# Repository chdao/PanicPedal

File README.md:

# PanicPedal

A wireless pedal system using ESP-NOW for low-latency communication between pedal transmitters and a USB HID keyboard receiver. Perfectly adequate for arcade gaming!

**Original Design**: This project is based on the [Perfectly Adequate Arcade Pedal (Wireless)](https://www.printables.com/model/1220746-perfectly-adequate-arcade-pedal-wireless) design on Printables. All initial ideas and the pedal model come from that design.

**PCB Project**: The custom PCB design is called **PanicPedal Pro** and includes an ESP32-S3-WROOM with automatic pedal detection. See `kicad-pcb/` for the KiCad project files and `esp32/panicpedal-pro/` for the firmware.

**⚠️ IMPORTANT CORRECTION**: The original schematic shows TP4056 OUT+ connected to the 3V3 pin. This is **INCORRECT** and can damage the ESP32. The TP4056 OUT+ must connect to **VCC** instead. See the [Wiring Diagram](#wiring-diagram) section below for the correct connections.

## Overview

This project consists of:
- **Transmitters**: ESP32-based pedal devices that send key press/release events via ESP-NOW
  - **FireBeetle 2**: `esp32/firebeetle2/firebeetle2.ino` - Configurable single or dual pedal mode
  - **PanicPedal Pro**: `esp32/panicpedal-pro/panicpedal-pro.ino` - Custom PCB with automatic pedal detection (1 or 2 pedals)
- **Receiver**: ESP32-S2/S3 device that receives ESP-NOW messages and types keys via USB HID Keyboard (`esp32/receiver/receiver.ino`)

**Note**: `espnow-pedal.cpp` is included as a reference file showing the original implementation. The actual project files are in the `esp32/` directory.

## Features

- **Low latency**: ESP-NOW provides fast, direct communication without WiFi connection
- **Multiple pedal modes**: Supports single pedal (LEFT or RIGHT) or dual pedal configurations
- **Automatic pedal detection** (PanicPedal Pro): Automatically detects whether 1 or 2 pedals are connected using NC (normally-closed) contacts - no manual configuration needed
- **Press and hold**: Keys stay pressed until pedal is released
- **Independent operation**: Both pedals can be pressed simultaneously
- **Battery efficient**: Includes inactivity timeout and deep sleep support
- **Automatic discovery**: No manual MAC address configuration needed - transmitters automatically discover receivers
- **Automatic reconnection**: Transmitters automatically reconnect to receivers after reboot
- **Slot management**: Receiver tracks available slots and only accepts transmitters when slots are available
- **Grace period**: 30-second discovery period after receiver boot for initial pairing and verification

## Hardware Requirements

### Recommended Boards

**Transmitters:**
- [FireBeetle 2 ESP32-E](https://www.dfrobot.com/product-2195.html) - Optimized for low power consumption, ideal for battery-powered pedal transmitters
- **PanicPedal Pro** - Custom PCB project with ESP32-S3-WROOM featuring automatic pedal detection (see `esp32/panicpedal-pro/README.md` for details)

**Receiver:**
- [ESP32-S3-DevKitC-1-N16R8](https://www.amazon.com/dp/B0CC8NYXRG) - ESP32-S3 board with native USB support for HID Keyboard functionality

### Transmitter
- ESP32 (tested with FireBeetle 2 ESP32-E and ESP32-S3-WROOM for PanicPedal Pro)
- Pedal switches (normally-open, connected to GPIO with pull-up)
- Optional: LED for status indication
- **PanicPedal Pro**: Uses NC (normally-closed) contacts for automatic detection of connected pedals

### Receiver
- ESP32-S2 or ESP32-S3 (for USB HID Keyboard support)
- USB connection to computer

## Pin Configuration

### Transmitter
- **Single Pedal Mode**: Connect pedal switch to GPIO 13
- **Dual Pedal Mode**: 
  - LEFT pedal: GPIO 13
  - RIGHT pedal: GPIO 14
- **LED**: GPIO 2 (optional)

**Pinout Reference**: See [FireBeetle 2 ESP32-E Pinout](docs/FireBeetle2_ESP32-E_Pinout.md) for complete pin details.

### Receiver
- Uses USB for communication (no GPIO pins needed for functionality)

## Wiring Diagram

### Transmitter Power Wiring (FireBeetle 2 ESP32-E)

**⚠️ IMPORTANT**: The TP4056 charging board OUT+ must connect to **VCC**, NOT 3V3!

```
TP4056 Charging Board          FireBeetle 2 ESP32-E
─────────────────────          ─────────────────────
OUT+ (red wire)    ──────────> VCC (or PH2.0 battery connector)
OUT- (black wire)  ──────────> GND
B+                 ──────────> 18650 Battery +
B-                 ──────────> 18650 Battery -
IN+                ──────────> Power Switch
IN-                ──────────> GND
```

**Why VCC and not 3V3?**
- **VCC** is the input voltage pin that accepts battery voltage (3.7-4.2V) or USB voltage (~4.7V)
- **3V3** is a regulated 3.3V OUTPUT pin - connecting 4-5V to it can damage the ESP32
- The FireBeetle's onboard regulator converts VCC to 3.3V internally

### Transmitter Signal Wiring

```
Left Pedal Switch (NO)  ───> GPIO 13
Left Pedal Switch (COM) ───> GND

Right Pedal Switch (NO)  ───> GPIO 14 (dual mode only)
Right Pedal Switch (COM) ───> GND

LED (anode)            ───> GPIO 2 (optional)
LED (cathode)          ───> GND
```

**Note**: The original schematic may show a "Mode Select Switch" on GPIO 26 for selecting between Bluetooth and ESP-NOW modes. This code uses ESP-NOW only, so that switch is not needed. Pedal mode (single/dual) is configured via the `PEDAL_MODE` define in the code.

**Note**: Switches should be normally-open (NO) type. The ESP32's internal pull-up resistors keep the pins HIGH when switches are open, and LOW when pressed.

## Setup and Usage

For detailed setup instructions, usage guide, configuration options, debug monitor setup, and troubleshooting, see [INSTRUCTIONS.md](INSTRUCTIONS.md).

## License

This project is provided as-is for educational and personal use.

## Contributing

Feel free to submit issues or pull requests for improvements!

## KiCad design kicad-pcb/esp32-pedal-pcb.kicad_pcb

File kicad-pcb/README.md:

# ESP32 Pedal PCB Design

KiCad project for a custom ESP32-based pedal PCB.

## Images

*Complete schematic diagram*

*PCB layout and routing*

*3D visualization of the PCB*

*Reference: FireBeetle 2 ESP32-E board (for comparison)*

## Specifications

- **Board Size**: 215.9mm x 25.4mm (8.5" x 1")
- **MCU**: ESP32-S3-WROOM-1 (native USB support)
- **Power**: USB-C charging + LiPo battery
- **Features**:
  - USB-C port (charging + data/programming)
  - Battery charging with TP4056
  - Battery voltage monitoring (ADC)
  - Status LED (green)
  - RGB LED (charger status, user-controllable)
  - Auto-reset circuit
  - Battery protection

## Circuit Sections

### 1. Power Management
- **USB-C Input**: VBUS with 5.1kΩ CC pull-downs
- **Battery Charger**: TP4056 (500mA charging current)
- **Battery Protection**: DW01A + FS8205A MOSFETs
- **3.3V Regulator**: AMS1117-3.3 or AP2112K-3.3
- **Battery Monitor**: Voltage divider (2x 100kΩ) to GPIO34

### 2. ESP32-S3-WROOM-1
- Native USB support (no USB-UART bridge needed)
- USB D+/D- connected directly to ESP32-S3
- Auto-reset circuit (DTR/RTS control)
- Boot button (GPIO0)
- Reset button (EN)

### 3. LEDs
- **Green Status LED**: GPIO2 → 330Ω → LED → GND
- **RGB LED**: 
  - Red: GPIO16 → 330Ω → R pin
  - Green: GPIO17 → 330Ω → G pin
  - Blue: GPIO18 → 330Ω → B pin
  - Common cathode → GND

### 4. Battery Monitoring
- Battery voltage divider: VBAT → 100kΩ → GPIO34 → 100kΩ → GND
- Charger status: TP4056 STAT pin → GPIO35

## GPIO Assignments

```
GPIO0:  Boot button (pulled high, button to GND)
GPIO2:  Green status LED
GPIO16: RGB LED - Red
GPIO17: RGB LED - Green  
GPIO18: RGB LED - Blue
GPIO21: Pedal switch
GPIO34: Battery voltage (ADC, input only)
GPIO35: Charger status (ADC, input only)
EN:     Reset button (pulled high, button to GND)
```

## Components List (BOM)

### ICs
- U1: ESP32-S3-WROOM-1 (or WROOM-1-N4R8)
- U2: TP4056 (battery charger)
- U3: AMS1117-3.3 or AP2112K-3.3 (3.3V regulator)
- U4: DW01A (battery protection)
- Q1, Q2: FS8205A (dual MOSFET for protection)

### Connectors
- J1: USB-C receptacle (16-pin or 24-pin)
- J2: JST-PH 2-pin (battery connector)

### LEDs
- D1: Green LED (3mm or 0805 SMD)
- D2: RGB LED common cathode (5mm or SMD)

### Resistors (0805 SMD or through-hole)
- R1: 330Ω (green LED)
- R2, R3, R4: 330Ω (RGB LED)
- R5, R6: 100kΩ (battery voltage divider)
- R7, R8: 5.1kΩ (USB-C CC pull-down)
- R9: 10kΩ (EN pull-up)
- R10: 2kΩ (TP4056 charging current - 500mA)
- R11, R12: 10kΩ (GPIO0 pull-up, optional)

### Capacitors (0805 SMD or through-hole)
- C1, C2: 10µF (USB input filtering)
- C3, C4: 10µF (3.3V regulator output)
- C5-C10: 100nF (decoupling for ESP32, ICs)
- C11: 100nF (EN reset filter)

### Buttons
- SW1: Tactile switch (reset)
- SW2: Tactile switch (boot/GPIO0)

### Battery
- 1S LiPo (3.7V nominal, 4.2V max)
- Capacity: 500mAh - 2000mAh (your choice)

## PCB Layout Notes

Given the 215.9mm x 25.4mm constraint:
- **4-layer PCB**
  - Layer 1 (Top): Component placement and signal routing
  - Layer 2: Power planes and routing
  - Layer 3: Ground plane
  - Layer 4 (Bottom): Signal routing
- **Component placement**:
  - USB-C connector at one end
  - Battery connector at opposite end
  - ESP32 module in center
  - LEDs near ESP32 for visibility
  - Charging IC near USB-C
  - Regulator between battery and ESP32
- **USB differential pairs**: Keep D+/D- traces matched length, ~90Ω impedance
- **Mounting holes**: 4x M3 holes at corners (optional)

## Design Status

✅ **COMPLETE** - Schematic and PCB layout are complete. See images above for visual reference.

## Notes

- KiCad 7.0 or later required
- Custom Espressif symbol and footprint libraries included in this directory
- Design files are tracked in git (temporary files excluded via `.gitignore`)

## Design Files

All design files are included in this directory:
- `esp32-pedal-pcb.kicad_pro` - KiCad project file
- `esp32-pedal-pcb.kicad_sch` - Schematic
- `esp32-pedal-pcb.kicad_pcb` - PCB layout
- `esp32-pedal-pcb.kicad_dru` - Design rules
- `esp32-pedal-pcb.rules` - Custom design rules
- `esp32-pedal-pcb.csv` - Bill of Materials (BOM)

## TODO

- [x] Complete schematic
- [x] Create PCB layout
- [x] Design rule check (DRC)
- [x] Generate BOM
- [ ] Generate Gerber files
- [ ] Create assembly drawings

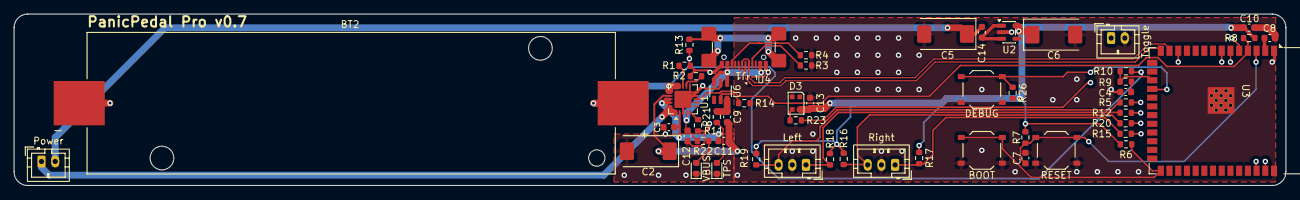
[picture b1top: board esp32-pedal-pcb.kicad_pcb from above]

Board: 4 copper layers, 185.5 x 25.0 mm, 54 parts (0 on the bottom side), 40 nets.

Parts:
BOOT1: TS-1187A-C-E-B; SW_Push_1P1T_XKB_TS-1187A
BT2: Keystone 1042P; BAT_1042P
C2, C5: 47µF; CP_EIA-7343-31_Kemet-D
C3, C4, C8, C11, C12, C13, C14: 0.1µF; C_0603_1608Metric
C6: 100µF; CP_EIA-7343-31_Kemet-D
C7, C10: 1µF; C_0603_1608Metric
C9: 10µF; C_0603_1608Metric
D1: 19-217/R6C-AL1M2VY/3T; LED_0603_1608Metric
D2: 19-217/GHC-YR1S2/3T; LED_0603_1608Metric
D3: WS2812B-2020; LED_WS2812B-2020_PLCC4_2.0x2.0mm
DEBUG1: TS-1187A-C-E-B; SW_Push_1P1T_XKB_TS-1187A
J1: USB4110-GF-A; USB_C_Receptacle_GCT_USB4110
Pedal1, Pedal2: B3B-PH-K-S(LF)(SN); JST_PH_B3B-PH-K_1x03_P2.00mm_Vertical
R1: 2.0kΩ; R_0603_1608Metric
R2: 20kΩ; R_0603_1608Metric
R3, R4: 5.1kΩ; R_0603_1608Metric
R5, R12, R15, R20: 100Ω; R_0603_1608Metric
R6, R7, R8, R11, R16, R17, R18, R19, R26: 10kΩ; R_0603_1608Metric
R9: 100kΩ; R_0603_1608Metric
R10: 360kΩ; R_0603_1608Metric
R13: 0Ω; R_0603_1608Metric
R14: 49.9k; R_0603_1608Metric
R21, R22: 2.2kΩ; R_0603_1608Metric
R23: 150Ω; R_0603_1608Metric
RESET1: TS-1187A-C-E-B; SW_Push_1P1T_XKB_TS-1187A
SW1, SW2: B2B-PH-K-S(LF)(SN); JST_PH_B2B-PH-K_1x02_P2.00mm_Vertical
U1: MCP73871T-2CCI/ML; QFN-20-1EP_4x4mm_P0.5mm_EP2.5x2.5mm
U2: TLV75733PDBV; SOT-23-5
U3: ESP32-S3-WROOM-1-N8; ESP32-S3-WROOM-1
U4: TPD2EUSB30ADRTR; Texas_DRT-3
U6: TPS2553DBVR; SOT95P280X145-6N

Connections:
/3V3: C6.1, C10.1, C13.1, D3.4 (VDD), R6.1, R7.1, R8.1, R16.2, R17.1, R18.1, R19.2, R26.1, U2.5 (OUT)
/5V: SW1.1 (A), U1.1 (OUT), U1.20 (OUT)
/5V SWITCHED: C5.1, C14.1, SW1.2 (B)
/D+: J1.A6 (D+), J1.B6 (D+), U3.14 (GPIO20/U1CTS/ADC2_CH9/CLK_OUT1/USB_D+), U4.1 (D+)
/D-: J1.A7 (D-), J1.B7 (D-), U3.13 (GPIO19/U1RTS/ADC2_CH8/CLK_OUT2/USB_D-), U4.2 (D-)
/EN: C7.1, R7.2, RESET1.2, U3.3 (EN)
/GPIO0: BOOT1.1, R6.2, U3.27 (GPIO0/BOOT)
/GPIO1: R20.1, U3.39 (GPIO1/TOUCH1/ADC1_CH0)
/GPIO2: R15.2, U3.38 (GPIO2/TOUCH2/ADC1_CH1)
/GPIO4/LBO: R8.2, U1.8 (STAT1/~LBO), U3.4 (GPIO4/TOUCH4/ADC1_CH3)
/GPIO5: SW2.1 (A), U3.5 (GPIO5/TOUCH5/ADC1_CH4)
/GPIO6: R12.2, U3.6 (GPIO6/TOUCH6/ADC1_CH5)
/GPIO7: R5.1, U3.7 (GPIO7/TOUCH7/ADC1_CH6)
/GPIO8: R23.1, U3.12 (GPIO8/TOUCH8/ADC1_CH7/SUBSPICS1)
/GPIO9: R9.2, R10.2, U3.17 (GPIO9/TOUCH9/ADC1_CH8/FSPIHD/SUBSPIHD)
/GPIO10: DEBUG1.1, R26.2, U3.18 (GPIO10/TOUCH10/ADC1_CH9/FSPICS0/FSPIIO4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)
/MCP IN: C3.1, C11.2, U1.2 (VPCC), U1.18 (IN), U1.19 (IN)
/SHIELD: J1.S1 (SHIELD), R13.1
/THERM: R11.1, U1.5 (THERM)
/TPS OUT: C9.1, R21.1, U6.6 (OUT)
/VBAT: BT2.P, R10.1, U1.14 (V_{BAT}), U1.15 (V_{BAT}), U1.16 (V_{BAT_SENSE})
/VBUS: C12.2, J1.A4 (VBUS), J1.A9 (VBUS), J1.B4 (VBUS), J1.B9 (VBUS), R22.1, U1.4 (PROG2), U6.1 (IN), U6.3 (EN)
GND: BOOT1.2, BT2.N, C2.2, C3.2, C4.1, C5.2, C6.2, C7.2, C12.1, C13.2, D1.1 (K), D2.1 (K), D3.2 (VSS), DEBUG1.2, J1.A1 (GND), J1.A12 (GND), J1.B1 (GND), J1.B12 (GND), Pedal1.2, Pedal2.2, R1.2, R2.2, R3.1, R4.1, R11.2, R13.2, R14.2, RESET1.1, SW2.2 (B), U1.3 (SEL), U1.9 (~TE), U1.10 (V_{SS}), U1.11 (V_{SS}), U1.21 (V_{SS}), U2.2 (GND), U3.1 (GND), U3.40 (GND), U3.41 (GND), U4.3 (GND), U6.2 (GND)
unnamed: C4.2, R9.1
unnamed: C8.1, C10.2
unnamed: D1.2 (A), R22.2
unnamed: D2.2 (A), R21.2
unnamed: D3.3 (DIN), R23.2
unnamed: J1.A5 (CC1), R3.2
unnamed: J1.B5 (CC2), R4.2
unnamed: Pedal1.1, R12.1, R18.2
unnamed: Pedal1.3, R5.2, R19.1
unnamed: Pedal2.1, R15.1, R17.2
unnamed: Pedal2.3, R16.1, R20.2
unnamed: C2.1, C9.2, C11.1, U1.17 (CE)
unnamed: R1.1, U1.13 (PROG1)
unnamed: R2.1, U1.12 (PROG3)
unnamed: C14.2, U2.1 (IN), U2.3 (EN)
unnamed: C8.2, U3.2 (3V3)
unnamed: R14.1, U6.5 (ILIM)

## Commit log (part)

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2025-12-31 Initial commit: ESP-NOW Pedal Keyboard system
2025-12-31 Update repository name to ESPNow Perfectly Adequate Arcade Pedal
2025-12-31 Fix: Add delay after WiFi initialization to ensure MAC address is readable
2025-12-31 Add recommended board links to README
2026-01-01 Add schematic correction: TP4056 OUT+ should connect to VCC not 3V3
2026-01-01 Add instructions for grounding GPIO 0 (D5) to enter download mode
2026-01-01 Implement auto-discovery pairing with EEPROM persistence
    - Transmitters automatically discover and pair with receivers on boot
    - Receiver assigns keys based on pairing order (first='l', second='r')
    - Dual pedals count as 2 slots, single pedals as 1 slot
    - Pairing state saved to EEPROM and persists across reboots
    - Unresponsive transmitters removed after 30 seconds
    - Simplified key mapping: pin 13 sends '1', pin 14 sends '2'
2026-01-02 Clean up unused code and fix logic issues
    - Remove unused MSG_ALIVE reply code from transmitter when paired
    - Remove useless sendPedalEvent calls when not paired
    - Fix handlePedal logic flow to only send events when paired
    - Remove misleading comment in receiver
    - Remove unused MSG_MAC_BROADCAST code from transmitter
    - All code is now clean and optimized
2026-01-02 Implement transmitter replacement mechanism
    - When new transmitter comes online and receiver is full, ping all paired transmitters
    - Remove transmitters that don't respond to MSG_ALIVE within 2 seconds
    - Send MSG_ALIVE to new transmitter to allow it to pair
    - Allows new transmitters to replace unresponsive ones automatically
2026-01-02 Fix debug monitor message mangling by removing incorrect null termination
    The debug monitor was placing a null terminator at msg.message[len-1] which was overwriting part of the actual message content. Since senders already properly null-terminate their messages, this was 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
2026-01-02 Optimize power consumption and improve debug output
    Transmitter Power Optimizations:
    - Reduced inactivity timeout from 10min to 2min for faster deep sleep
    - Dynamic loop delay: 10ms after pedal press, 20ms when idle (adaptive responsiveness)
    - Reduced WiFi TX power from 20dBm to 10dBm (pedals are close to receiver)
    - Activity boost window: 2 seconds of maximum responsiveness after each press
    Debug Output Improvements:
2026-01-02 Add KiCad PCB project directory (git-ignored)
    Added:
    - kicad-pcb/ directory for ESP32 pedal PCB design
    - Added kicad-pcb/ to .gitignore
    - Created project file and README with specifications
    - Board: 215.9mm x 25.4mm
    - ESP32-S3-WROOM with USB-C, battery charging, LEDs
2026-01-04 Add KiCad PCB design files to repository
    - Add main project files (.kicad_pro, .kicad_sch, .kicad_pcb)
    - Add custom Espressif symbol and footprint libraries
    - Add library table files (sym-lib-table, fp-lib-table)
    - Add README.md documentation
    - Update .gitignore to exclude temporary/generated files only
2026-01-04 Add PCB design reference to main README with untested status
2026-01-04 Update PCB README: 4-layer board with ground plane on layer 3
2026-01-05 Update PCB schematic
2026-01-05 Update PCB documentation images and layout
2026-01-05 Update shared/messages.h with all utilities and message types
2026-01-05 Remove duplicate getSlotsNeeded from receiver (now in shared/messages.h)
2026-01-07 Update PCB schematic and layout files
2026-01-07 Add KiCad lock files to gitignore and remove from tracking
2026-01-08 Fix USB DATA+/- pin connections and add proper bulk capacitors
2026-01-08 Set PanicPedal Pro default to single pedal mode (GPIO7)
2026-01-08 Update PCB files and documentation images
    - Update KiCad PCB project files (kicad_pcb, kicad_prl, kicad_pro, kicad_sch)
    - Update documentation images (3D_render.png, PCB_routing.png, schema.png)
    - Add new PCB backup files
    - Remove old backup files
2026-01-08 Add firmware version check for pedal mode detection
    - Store firmware version in NVS along with pedal mode
    - Compare stored version with current version on boot
    - Re-run detection if firmware version changes
    - Detection now runs on first boot and after firmware updates
    - Increment FIRMWARE_VERSION to force re-detection
2026-01-08 Add PanicPedal Pro automatic pedal detection to main README
    - Document PanicPedal Pro transmitter with automatic detection
    - Add automatic pedal detection feature to Features section
    - Update Hardware Requirements section
    - Update configuration instructions for PanicPedal Pro
    - Explain that PanicPedal Pro auto-detects 1 vs 2 pedals
2026-01-08 Update configuration section for PanicPedal Pro auto-detection
2026-01-08 Add PanicPedal Pro PCB project name to README
2026-01-09 Add APA102-2020 LED control for PanicPedal Pro
    - Create LEDService infrastructure module with APA102 protocol implementation
    - Implement bit-banging SPI for APA102 LED communication
    - Add LED states: OFF, PAIRING (blinking blue), PAIRED (solid green), PEDAL_PRESS (white flash), ERROR (blinking red)
    - Integrate LED control with pairing and pedal events
    - LED shows pairing state when searching for receiver
    - LED shows green when paired
2026-01-09 Add missing pedalService_setLEDService implementation
2026-01-09 Update LED behavior: off after pairing, only on when charging
    - Turn LED off after successful pairing (saves battery)
    - Remove LED flash on pedal press
    - Add charging detection using GPIO4 (STAT1/LBO from MCP73871)
    - LED shows green when charging, off otherwise
    - Update LED_STATE_PAIRED to turn LED off instead of green
2026-01-09 Add charging detection to LED control loop
2026-01-12 Update GPIO pins: Pedal1 NO=GPIO2, Pedal2 NO=GPIO1
2026-01-12 Add JLCPCB and production directories to .gitignore
2026-01-12 Add *.zip to .gitignore
2026-01-12 Convert pedal detection from polling to event-driven interrupts
    - Add GPIO interrupts on pedal pins (CHANGE mode)
    - ISR functions set interrupt flags (IRAM_ATTR for ESP32)
    - Main loop processes interrupts with debouncing
    - Eliminates continuous polling, improves battery life
    - Pedal presses now trigger immediately on state change
2026-01-12 Eliminate polling: read GPIO only in ISR and when verifying debounce
    - Read GPIO state once in ISR when interrupt fires (stored in newState)
    - Only process pedals when interrupts occur or debouncing needs checking
    - Eliminate unnecessary GPIO reads - use state captured in ISR
    - Only read GPIO again after debounce delay to verify stable state
    - pedalReader_update() returns immediately if no work needed
    - Significantly reduces power consumption by avoiding continuous polling
2026-01-12 Apply interrupt-driven pedal detection to FireBeetle 2
    - Convert from polling to event-driven interrupts
    - Read GPIO state once in ISR when interrupt fires
    - Only process pedals when interrupts occur or debouncing needs checking
    - Eliminate unnecessary GPIO reads for better power efficiency
    - Same optimizations as PanicPedal Pro
2026-01-12 Fix PedalService.h includes to use shared PedalReader location
2026-01-12 Standardize debug message formatting and add debug monitor support
    - Created shared debug_format.h/cpp for consistent debug message formatting
    - Updated transmitter and receiver to use shared debug formatting code
    - Debug messages now use format: [MAC] [R/T] [timestamp] message
    - MAC address shown by debug monitor from ESP-NOW packet info
    - Added NVRAM persistence for debug toggle state on FireBeetle 2
    - Transmitter sends debug messages to debug monitor when debug enabled
2026-01-14 Fix watchdog timeouts and stabilize interrupt handling
    - Simplified interrupt handling: removed interrupt detachment/reattachment
    - Reduced debounce time from 200ms to 50ms for better responsiveness
    - Removed excessive yield() calls that were causing instability
    - Fixed panic issues when pedal is held down
    - Fixed panic issues when pedal is not paired
    - Fixed activity timer reset when pedal is pressed
2026-01-15 Wake from deep sleep on either pedal (GPIO1/GPIO2)
2026-01-15 Tighten debug logging + shrink PairingService helpers
2026-01-16 Update PCB schematics and design files
2026-01-16 Update pairing flow: transmitter replies with MSG_PAIRING_CONFIRMED, fix timing, add LED breathing effect
2026-01-16 Fix MSG_PAIRING_CONFIRMED_ACK flow and debug monitor visibility
    - Transmitter sends MSG_PAIRING_CONFIRMED to saved receiver on deep sleep wake
    - Receiver always responds with MSG_PAIRING_CONFIRMED to known transmitters sending MSG_TRANSMITTER_ONLINE
    - Transmitter replies with MSG_PAIRING_CONFIRMED_ACK (new message type 0x09)
    - Transmitter sends MSG_DELETE_RECORD if receiving MSG_PAIRING_CONFIRMED from different receiver
    - Defer debug messages from ESP-NOW callback to main loop to ensure reliable broadcast
    - Increase delays after ESP-NOW sends to ensure stack is ready for debug broadcasts
2026-01-16 Rename project to PanicPedal in README
2026-01-16 Fix pairing flow: receiver responds with MSG_PAIRING_CONFIRMED_ACK to transmitter's MSG_PAIRING_CONFIRMED
    - Receiver now sends MSG_PAIRING_CONFIRMED_ACK when receiving MSG_PAIRING_CONFIRMED from transmitter
    - Transmitter handles MSG_PAIRING_CONFIRMED_ACK from receiver (restores pairing, no reply needed)
    - Updated documentation to reflect new flow
2026-01-16 Only send MSG_TRANSMITTER_ONLINE when needed: no MAC saved or MSG_PAIRING_CONFIRMED timeout
    - Transmitter only sends MSG_TRANSMITTER_ONLINE if no MAC saved (for discovery)
    - If MSG_PAIRING_CONFIRMED is sent and no ACK received within 1s, send MSG_TRANSMITTER_ONLINE
    - Track MSG_PAIRING_CONFIRMED send time and waiting flag
    - Clear waiting flag when MSG_PAIRING_CONFIRMED_ACK is received
    - Added PAIRING_CONFIRMED_TIMEOUT_MS constant (1 second)
2026-01-16 Fix stuck key issue: detect pedal release during deep sleep wake initialization
    - Track which specific pedals were pressed on wakeup (pedal1PressedOnWakeup, pedal2PressedOnWakeup)
    - Update PedalReader's lastState to LOW after sending press event on wake
    - After attaching interrupts, check if pedals were released during initialization
    - If pedal is HIGH (released) but lastState is LOW (we sent a press), send release event
    - Handles both single and dual pedal modes correctly
    - Prevents keys from getting stuck as 'down' if released during initialization
2026-01-20 Unify debug messaging across all devices using shared DebugService
    - Enhanced DebugService to support both EspNowTransport (transmitters) and ReceiverEspNowTransport (receiver) via function pointers
    - Migrated receiver from DebugMonitor module to shared DebugService
    - Added setDeviceType() to correctly tag debug messages with device type
    - Fixed grace period timing issue when clearing MAC addresses (use currentTime instead of millis())
    - Improved debug messages to distinguish between no transmitters loaded vs no replies
    - All devices now use the same code for sending debug messages to debug monitor

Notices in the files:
kicad-pcb/esp32-pedal-pcb.kicad_pcb:
©2026
